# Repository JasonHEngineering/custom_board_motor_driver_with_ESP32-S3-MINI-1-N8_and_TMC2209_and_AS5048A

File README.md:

# Custom board motor driver with_ESP32-S3-MINI-1-N8, TMC2209 and AS5048A
A custom board (42x42 mm - Nema 17) for driving bipolar stepper motors. Integrated with AS5048A - 14 bit absolute rotary encoder and TMC2209 silent stepper driver. Microstepping is programmable up to 64 micro-steps while max current draw capped by current sense R to be at 1.7A.

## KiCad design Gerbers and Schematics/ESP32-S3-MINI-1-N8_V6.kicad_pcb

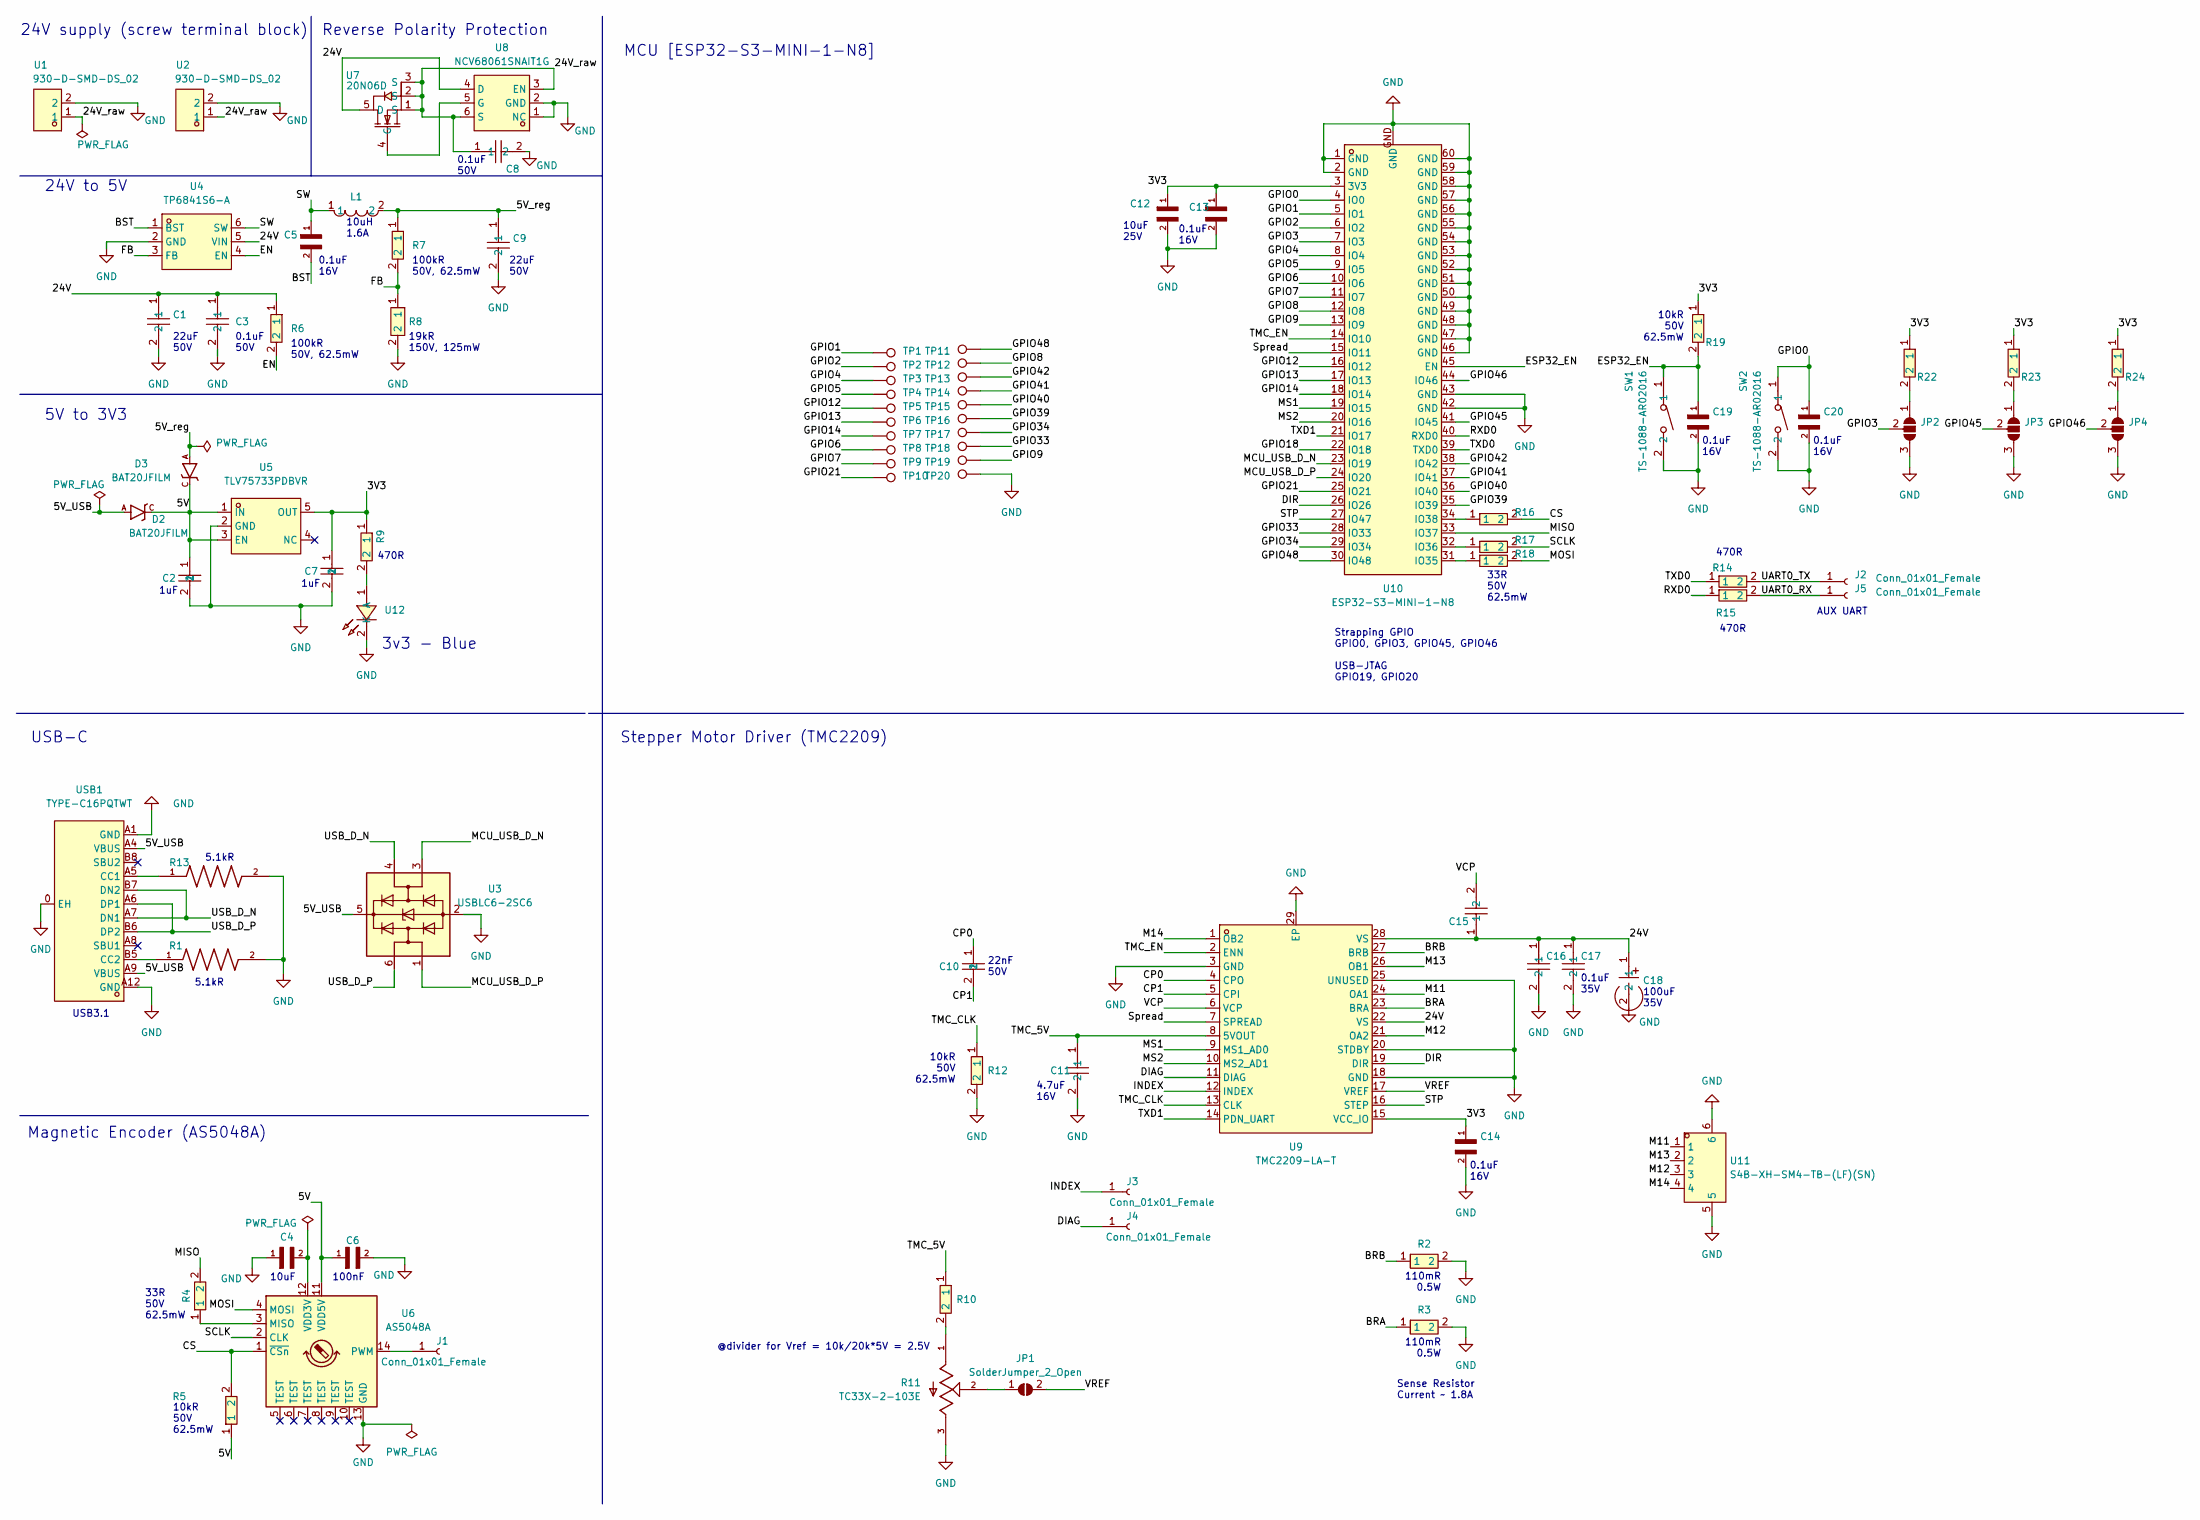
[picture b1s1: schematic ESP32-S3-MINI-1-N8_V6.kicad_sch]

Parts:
C1, C9: FS55X226K500EHG; Cap_MLCC_50V_22uF_X7R_2220_C784103; LCSC Part C784103
C2, C7: CC0603KRX7R7BB105; MLCC_16V_1uF_X7R_±10%_0603_C106248; LCSC Part C106248
C3, C8: CC0603KRX7R9BB104; MLCC_Yageo_50V_100nF_X7R_±10%_0603_C14663; LCSC Part C14663
C4: GRM155R60J106ME15D; CAPC1005X65N; LCSC C412251
C5, C13, C14, C19, C20: GCM155R71C104KA55J; CAPC1005X55N; LCSC Part # C2655418
C6: GCM155R71C104KA55J; CAPC1005X55N; LCSC C2655418
C10: GRM155R71H223KA12D; MLCC_Murata_50V_22nF_X7R_±10%_0402_C77023; LCSC Part C77023
C11: GRM188Z71C475KE21D; C0603; LCSC Part C389010
C12: GRM21BR61E106KA73L; CAPC2012X140N; LCSC Part # C84416
C15, C16, C17: CGA2B3X7R1V104KT0Y0F; C0402_L1.0-W0.5-H0.5; LCSC Part C343047
C18: RVT1V101M0605; Capacitor_100uF_35V_75mA@120Hz_±20%_D6pt3xL5pt4mm_C3151830; LCSC Part C3151830
D2, D3: BAT20JFILM; SOD-323; LCSC Part # C155590
J1, J2, J3, J4, J5: Conn_01x01_Female; PinHeader_1x01_P1.00mm_Vertical
JP1: SolderJumper_2_Open; SolderJumper-2_P1.3mm_Open_RoundedPad1.0x1.5mm
JP2, JP3, JP4: SolderJumper_3_Open; SolderJumper-3_P1.3mm_Open_RoundedPad1.0x1.5mm
L1: FTC252012S100MBCA; Inductor_10uH_1pt6A_2x2pt5mm_C5832376; LCSC Part C5832376
R1, R13: RC0402FR-075K1L; RESC1005X40N; LCSC Part # C105872
R2, R3: RL1206FR-7W0R11L; Resistor_110mΩ_500mW_1206_C859923; LCSC Part C859923
R4, R16, R17, R18: RC0402FR-0733RL; Resistor_62.5mW_50V_±1%_33Ω_0402_C138002; LCSC Part C138002
R5, R10, R12, R19, R22, R23, R24: RC0402FR-0710KL; Resistor_62.5mW_50V_±1%_10kΩ_0402_C60490; LCSC Part C60490
R6, R7: RC0402FR-07100KL; Resistor_ 100kΩ_62.5mW_50V_0402_C60491; LCSC Part C60491
R8: FRC0805F1902TS; Resistor_19kΩ_0.125W_150V_0805_C2930177; LCSC Part C2930177
R9, R14, R15: 0402WGF4700TCE; Resistor_470Ω_62p5W_0402_C25117; LCSC Part C25117
R11: TC33X-2-103E; TRIM_TC33X-2-103E; LCSC Part # C719176
SW1, SW2: TS-1088-AR02016; 50mA_12V_1.6N__Tactile_Switches_C720477; LCSC Part C720477
TP1, TP2, TP3, TP4, TP5, TP6, TP7, TP8, TP9, TP10, TP11, TP12, TP13, TP14, TP15, TP16, TP17, TP18, TP19, TP20: TestPoint; TestPoint_Pad_1.0x1.0mm
U1, U2: 930-D-SMD-DS_02; WECO_1x2P_13.5A_Screw_Terminal_C19273347; LCSC Part C19273347
U3: USBLC6-2SC6; SOT-23-6; LCSC Part # C7519
U4: TP6841S6-A; SOT-23-6_L2.9-W1.6-P0.95-LS2.8-BL; LCSC Part C2844924
U5: TLV75733PDBVR; LDO_1A_Fixed_3.3V_out_5.5V_in_SOT-23-5_C485517; LCSC Part C485517
U6: AS5048A; TSSOP-14_4.4x5mm_P0.65mm; LCSC C2655181
U7: 20N06D; 60V_20A_28mΩ_2.5V_1-N-channel_PDFN-8(3x3)_MOSFETs_C7543835; LCSC Part C7543835
U8: NCV68061SNAIT1G; TSOP-6_L3.0-W1.5-P0.95-BL; LCSC Part C5206748
U9: TMC2209-LA-T; TRINAMIC_TMC2209-LA-T_C2150710; LCSC Part C2150710
U10: ESP32-S3-MINI-1-N8; BULETM-SMD_ESP32-S3-MINI-1-N8; LCSC Part C2913206
U11: S4B-XH-SM4-TB-(LF)(SN); CONN-SMD_S4B-XH-SM4-TB-LF-SN; LCSC Part C161861
U12: XL-1608UBC-06A; Blue_LED_5mA_456nm~476nm_130°_2.6V~3V_0603_C7371904; LCSC Part C7371904
USB1: TYPE-C16PQTWT; USB 3.1_C_3A_Surface_Mount_16P_C5187472; LCSC Part C5187472

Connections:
/3V3: C7.1, C12.1, C13.1, C14.1, R9.1, R19.1, R22.1, R23.1, R24.1, U5.5 (OUT), U9.15 (VCC_IO), U10.3 (3V3)
/5V: C2.1, C6.1, D2.C, D3.C, R5.1, U5.1 (IN), U5.3 (EN), U6.11 (VDD5V)
/5V_USB: D2.A, U3.5 (VBUS), USB1.A4 (VBUS), USB1.A9 (VBUS)
/5V_reg: C9.1, D3.A, L1.2, R7.1
/24V: C1.1, C3.1, C15.1, C16.1, C17.1, C18.1, R6.1, U4.5 (VIN), U7.5 (D), U8.4 (D), U9.22 (VS), U9.28 (VS)
/24V_raw: C8.1, U1.1, U2.1, U7.1 (S), U7.2 (S), U7.3 (S), U8.3 (EN), U8.6 (S)
/BRA: R3.1, U9.23 (BRA)
/BRB: R2.1, U9.27 (BRB)
/BST: C5.2, U4.1 (BST)
/CP0: C10.1, U9.4 (CPO)
/CP1: C10.2, U9.5 (CPI)
/CS: R5.2, R16.2, U6.1 (~CSn)
/DIAG: J4.1, U9.11 (DIAG)
/DIR: U9.19 (DIR), U10.26 (IO26)
/EN: R6.2, U4.4 (EN)
/ESP32_EN: C19.1, R19.2, SW1.1, U10.45 (EN)
/FB: R7.2, R8.1, U4.3 (FB)
/GPIO0: C20.1, SW2.1, U10.4 (IO0)
/GPIO1: TP1.1, U10.5 (IO1)
/GPIO2: TP2.1, U10.6 (IO2)
/GPIO3: JP2.2 (C), U10.7 (IO3)
/GPIO4: TP3.1, U10.8 (IO4)
/GPIO5: TP4.1, U10.9 (IO5)
/GPIO6: TP8.1, U10.10 (IO6)
/GPIO7: TP9.1, U10.11 (IO7)
/GPIO8: TP12.1, U10.12 (IO8)
/GPIO9: TP19.1, U10.13 (IO9)
/GPIO12: TP5.1, U10.16 (IO12)
/GPIO13: TP6.1, U10.17 (IO13)
/GPIO14: TP7.1, U10.18 (IO14)
/GPIO18: U10.22 (IO18)
/GPIO21: TP10.1, U10.25 (IO21)
/GPIO33: TP18.1, U10.28 (IO33)
/GPIO34: TP17.1, U10.29 (IO34)
/GPIO39: TP16.1, U10.35 (IO39)
/GPIO40: TP15.1, U10.36 (IO40)
/GPIO41: TP14.1, U10.37 (IO41)
/GPIO42: TP13.1, U10.38 (IO42)
/GPIO45: JP3.2 (C), U10.41 (IO45)
/GPIO46: JP4.2 (C), U10.44 (IO46)
/GPIO48: TP11.1, U10.30 (IO48)
/INDEX: J3.1, U9.12 (INDEX)
/M11: U9.24 (OA1), U11.1
/M12: U9.21 (OA2), U11.3
/M13: U9.26 (OB1), U11.2
/M14: U9.1 (OB2), U11.4
/MCU_USB_D_N: U3.3 (I/O2), U10.23 (IO19)
/MCU_USB_D_P: U3.1 (I/O1), U10.24 (IO20)
/MISO: R4.2, U10.33 (IO37)
/MOSI: R18.2, U6.4 (MOSI)
/MS1: U9.9 (MS1_AD0), U10.19 (IO15)
/MS2: U9.10 (MS2_AD1), U10.20 (IO16)
/RXD0: R15.1, U10.40 (RXD0)
/SCLK: R17.2, U6.2 (CLK)
/STP: U9.16 (STEP), U10.27 (IO47)
/SW: C5.1, L1.1, U4.6 (SW)
/Spread: U9.7 (SPREAD), U10.15 (IO11)
/TMC_5V: C11.1, R10.1, U9.8 (5VOUT)
/TMC_CLK: R12.1, U9.13 (CLK)
/TMC_EN: U9.2 (ENN), U10.14 (IO10)
/TXD0: R14.1, U10.39 (TXD0)
/TXD1: U9.14 (PDN_UART), U10.21 (IO17)
/UART0_RX: J5.1, R15.2
/UART0_TX: J2.1, R14.2
/USB_D_N: U3.4 (I/O2), USB1.A7 (DN1), USB1.B7 (DN2)
/USB_D_P: U3.6 (I/O1), USB1.A6 (DP1), USB1.B6 (DP2)
/VCP: C15.2, U9.6 (VCP)
/VREF: JP1.2 (B), U9.17 (VREF)
GND: C1.2, C2.2, C3.2, C4.1, C6.2, C7.2, C8.2, C9.2, C11.2, C12.2, C13.2, C14.2, C16.2, C17.2, C18.2, C19.2, C20.2, JP2.3 (B), JP3.3 (B), JP4.3 (B), R1.2, R2.2, R3.2, R8.2, R11.3, R12.2, R13.2, SW1.2, SW2.2, TP20.1, U1.2, U2.2, U3.2 (GND), U4.2 (GND), U5.2 (GND), U6.13 (GND), U8.1 (NC), U8.2 (GND), U9.3 (GND), U9.18 (GND), U9.20 (STDBY), U9.25 (UNUSED), U9.29 (EP), U10.1 (GND), U10.2 (GND), U10.42 (GND), U10.43 (GND), U10.46 (GND), U10.47 (GND), U10.48 (GND), U10.49 (GND), U10.50 (GND), U10.51 (GND), U10.52 (GND), U10.53 (GND), U10.54 (GND), U10.55 (GND), U10.56 (GND), U10.57 (GND), U10.58 (GND), U10.59 (GND), U10.60 (GND), U10.GND, U11.5, U11.6, U12.2 (K), USB1.0 (EH), USB1.A1 (GND), USB1.A12 (GND)
unnamed: C4.2, U6.12 (VDD3V)
unnamed: J1.1, U6.14 (PWM)
unnamed: JP1.1 (A), R11.2
unnamed: JP2.1 (A), R22.2
unnamed: JP3.1 (A), R23.2
unnamed: JP4.1 (A), R24.2
unnamed: R1.1, USB1.B5 (CC2)
unnamed: R4.1, U6.3 (MISO)
unnamed: R9.2, U12.1 (A)
unnamed: R10.2, R11.1
unnamed: R13.1, USB1.A5 (CC1)
unnamed: R16.1, U10.34 (IO38)
unnamed: R17.1, U10.32 (IO36)
unnamed: R18.1, U10.31 (IO35)
unnamed: U7.4 (G), U8.5 (G)

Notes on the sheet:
10uF
0.1uF 16V
22uF 50V
100kR 50V, 62.5mW
470R
5.1kR
Reverse Polarity Protection
Sense Resistor Current ~ 1.8A
110mR 0.5W
@divider for Vref = 10k/20k*5V = 2.5V
1uF
33R 50V 62.5mW
10kR 50V 62.5mW
USB3.1
5V to 3V3
USB-C
0.1uF 50V
0.1uF 35V
Strapping GPIO GPIO0, GPIO3, GPIO45, GPIO46 USB-JTAG GPIO19, GPIO20
19kR 150V, 125mW
24V supply (screw terminal block)
MCU [ESP32-S3-MINI-1-N8]
AUX UART
10uH 1.6A
Magnetic Encoder (AS5048A)
100uF 35V
24V to 5V
4.7uF 16V
10uF 25V
Stepper Motor Driver (TMC2209)
3v3 - Blue
100nF
22nF 50V

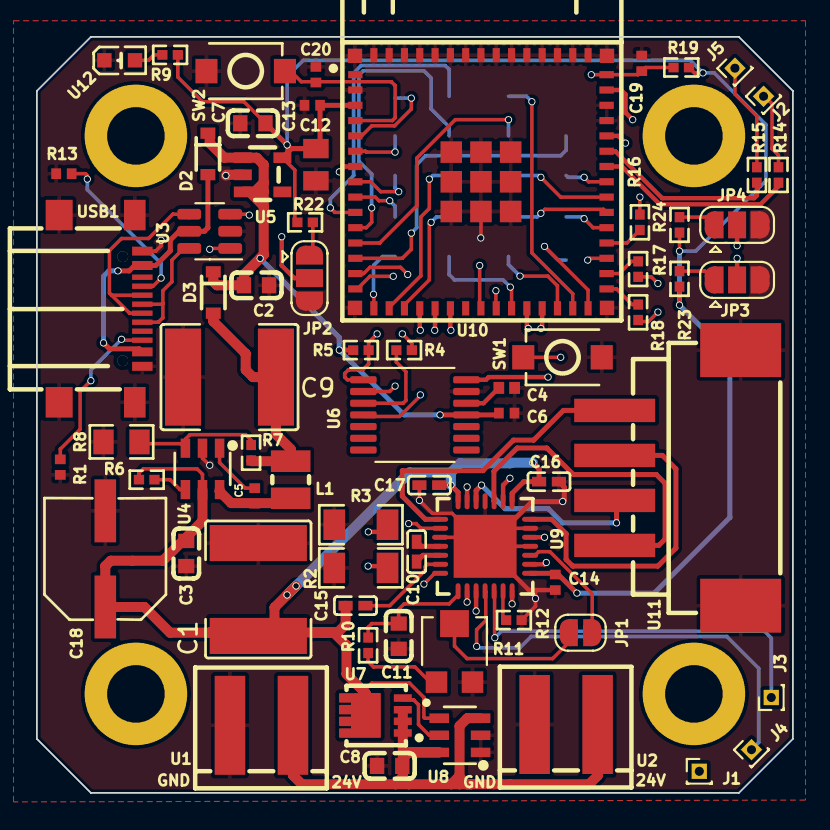
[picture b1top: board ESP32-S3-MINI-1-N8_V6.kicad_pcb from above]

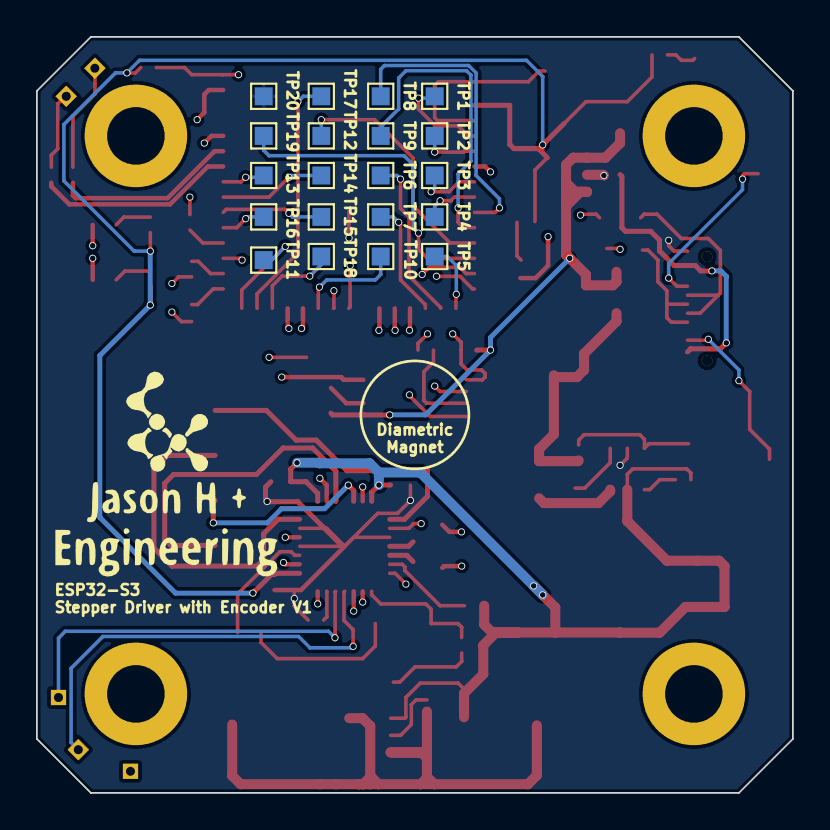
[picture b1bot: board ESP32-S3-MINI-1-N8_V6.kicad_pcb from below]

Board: 4 copper layers, 42.0 x 42.0 mm, 89 parts (20 on the bottom side), 83 nets.

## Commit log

2025-08-10 Initial upload
    Schematics, gerber and BOM
2025-08-10 Draft codes upload
2025-08-14 Added AS5048A_encoder_sanity_check_V1
